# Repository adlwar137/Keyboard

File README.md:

# Custom Keyboard

# 🚧 This is a work in progress 🚧

A custom mechanical keyboard deisgned and built from the ground up

## Features

- Custom PCB designed for the keyboard
- Custom case designed in CAD
- Custom firmware

## Design

### PCB

Designed from scratch in KICAD

### Case

Custom case designed in FreeCAD and 3D printed

## Firmware

Custom firmware the will be written in rust

## Folders

- `firmware/` - Keyboard firmware
- `pcb/` - PCB design files
- `artifacts/` - STLs, DXFs, and other exported files
- `screenshots/` - Screenshots of various parts during development

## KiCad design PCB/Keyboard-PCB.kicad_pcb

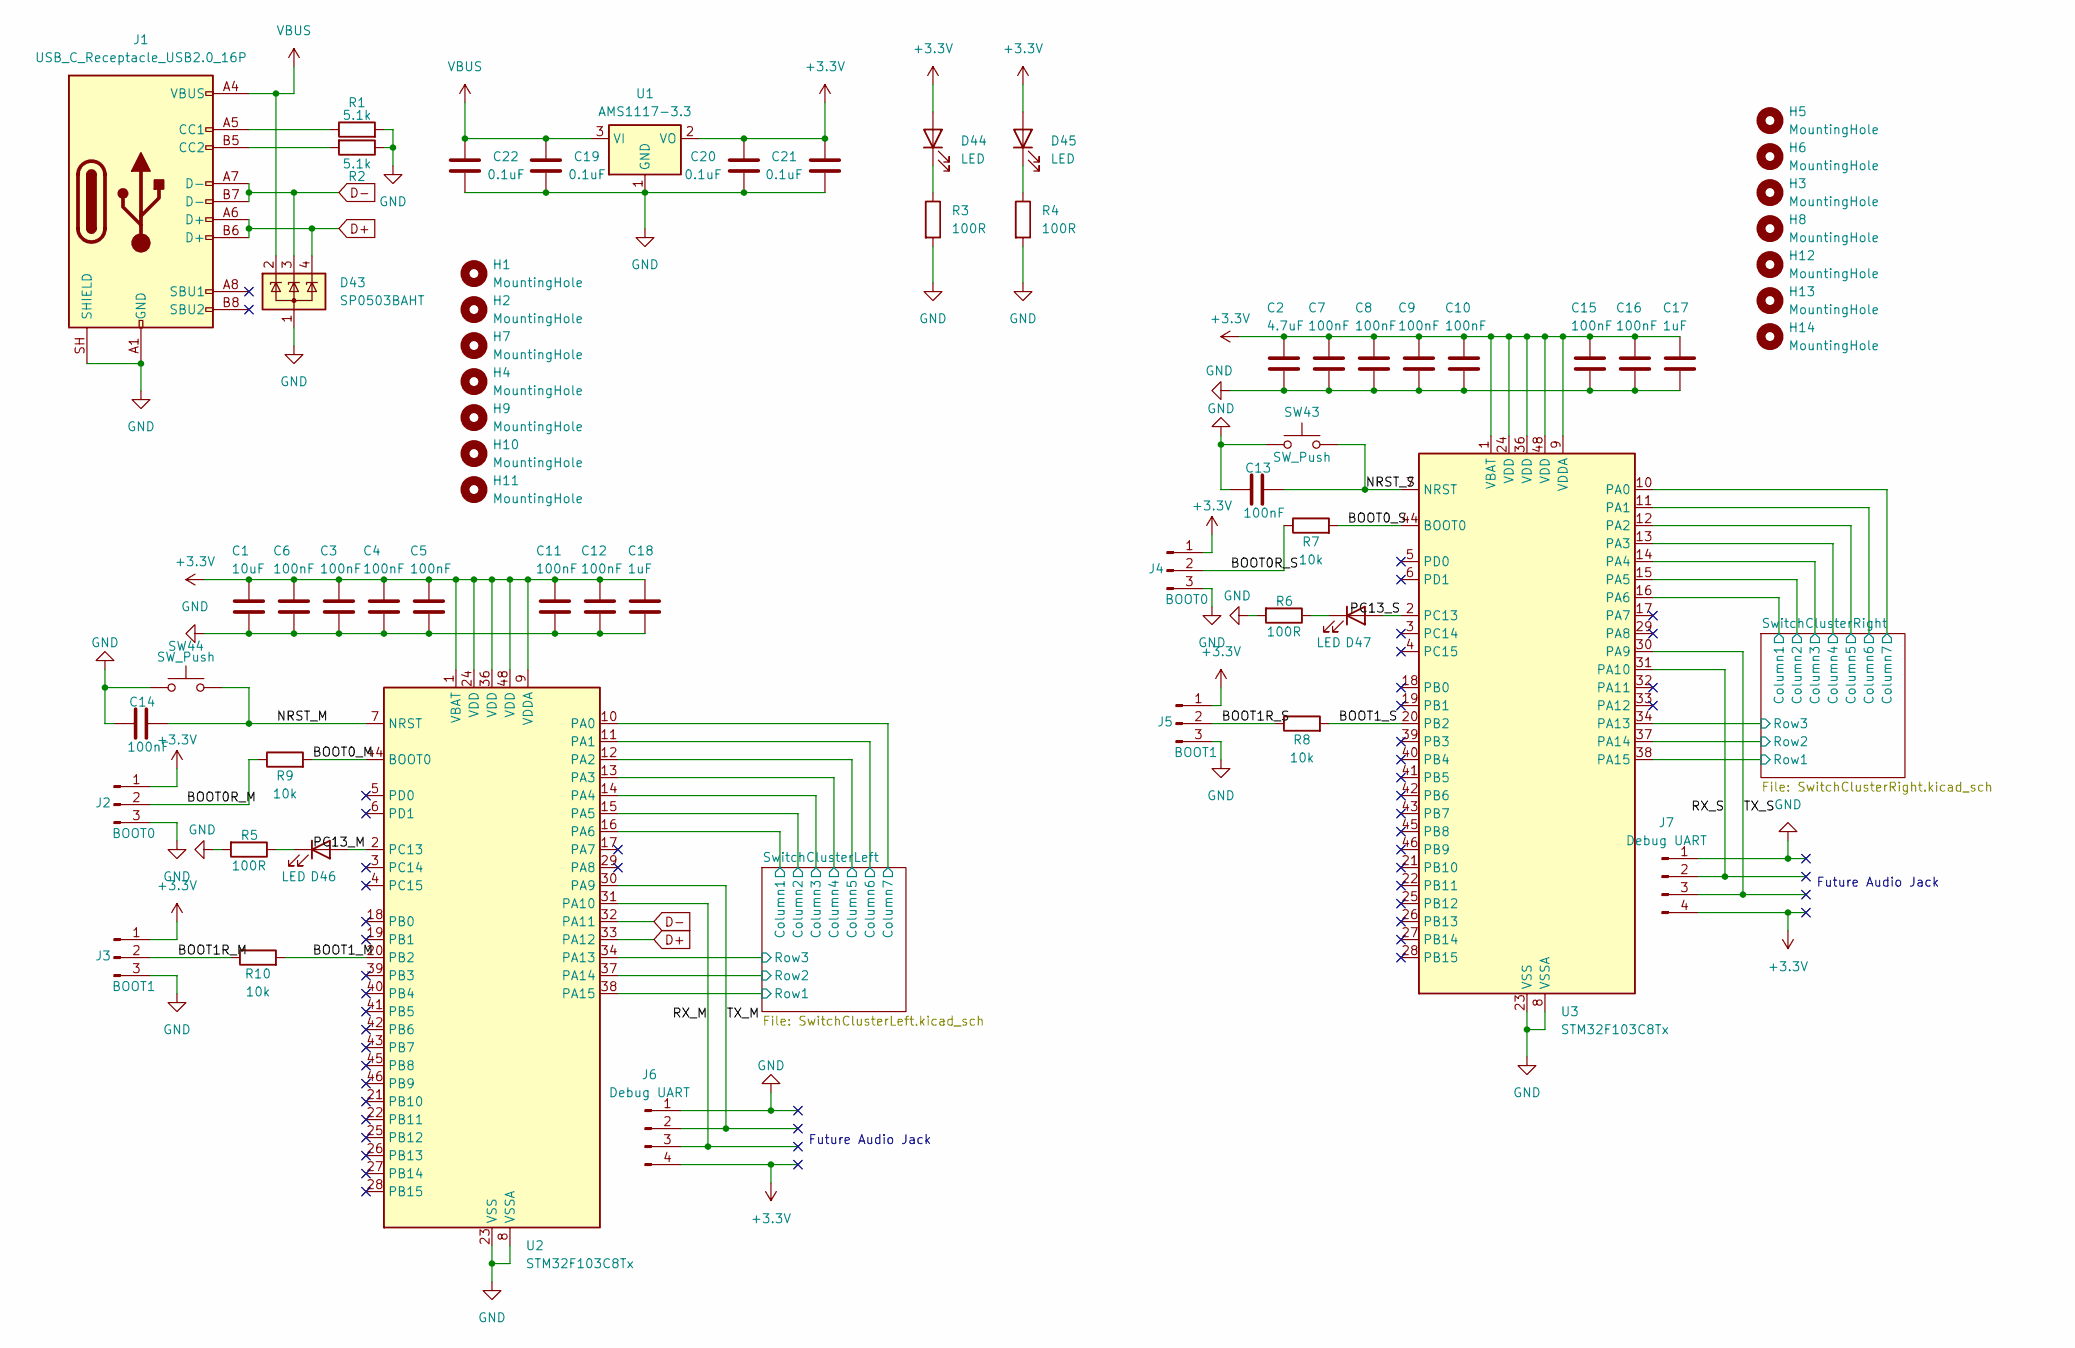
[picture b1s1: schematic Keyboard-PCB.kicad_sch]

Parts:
C1: 10uF; C_0402_1005Metric
C2: 4.7uF; C_0402_1005Metric
C3, C4, C5, C6, C7, C8, C9, C10, C11, C12, C13, C14, C15, C16: 100nF; C_0402_1005Metric
C17, C18: 1uF; C_0402_1005Metric
C19, C20, C21, C22: 0.1uF; C_0402_1005Metric
D43: SP0503BAHT; SOT-143
D44, D45, D46, D47: LED; LED_0805_2012Metric
H1, H2, H3, H4, H5, H6, H7, H8, H9, H10, H11, H12, H13, H14: MountingHole; MountingHole_3mm
J1: USB_C_Receptacle_USB2.0_16P; USB_C_Receptacle_GCT_USB4085
J2, J4: BOOT0; PinHeader_1x03_P2.54mm_Vertical
J3, J5: BOOT1; PinHeader_1x03_P2.54mm_Vertical
J6, J7: Debug UART; PinHeader_1x04_P2.54mm_Vertical
R1, R2: 5.1k; R_0805_2012Metric
R3, R4, R5, R6: 100R; R_0402_1005Metric
R7, R8, R9, R10: 10k; R_0805_2012Metric
SW43, SW44: SW_Push; SW_Push_1P1T_NO_CK_KMR2
U1: AMS1117-3.3; SOT-223-3_TabPin2
U2, U3: STM32F103C8Tx; LQFP-48_7x7mm_P0.5mm

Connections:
+3.3V: C1.1, C2.1, C3.1, C4.1, C5.1, C6.1, C7.1, C8.1, C9.1, C10.1, C11.1, C12.1, C15.1, C16.1, C17.1, C18.1, C20.1, C21.1, D44.2 (A), D45.2 (A), J2.1, J3.1, J4.1, J5.1, J6.4, J7.4, U1.2 (VO), U2.1 (VBAT), U2.9 (VDDA), U2.24 (VDD), U2.36 (VDD), U2.48 (VDD), U3.1 (VBAT), U3.9 (VDDA), U3.24 (VDD), U3.36 (VDD), U3.48 (VDD)
/BOOT0R_M: J2.2, R9.1
/BOOT0R_S: J4.2, R7.1
/BOOT0_M: R9.2, U2.44 (BOOT0)
/BOOT0_S: R7.2, U3.44 (BOOT0)
/BOOT1R_M: J3.2, R10.1
/BOOT1R_S: J5.2, R8.1
/BOOT1_M: R10.2, U2.20 (PB2)
/BOOT1_S: R8.2, U3.20 (PB2)
/NRST_M: C14.1, SW44.2, U2.7 (NRST)
/NRST_S: C13.1, SW43.2, U3.7 (NRST)
/PC13_M: D46.2 (A), U2.2 (PC13)
/PC13_S: D47.2 (A), U3.2 (PC13)
/RX_M: J6.3, U2.31 (PA10)
/RX_S: J7.2, U3.31 (PA10)
/SwitchClusterLeft/Column1: U2.16 (PA6); also elsewhere on the board
/SwitchClusterLeft/Column2: U2.15 (PA5); also elsewhere on the board
/SwitchClusterLeft/Column3: U2.14 (PA4); also elsewhere on the board
/SwitchClusterLeft/Column4: U2.13 (PA3); also elsewhere on the board
/SwitchClusterLeft/Column5: U2.12 (PA2); also elsewhere on the board
/SwitchClusterLeft/Column6: U2.11 (PA1); also elsewhere on the board
/SwitchClusterLeft/Column7: U2.10 (PA0); also elsewhere on the board
/SwitchClusterLeft/Row1: U2.38 (PA15); also elsewhere on the board
/SwitchClusterLeft/Row2: U2.37 (PA14); also elsewhere on the board
/SwitchClusterLeft/Row3: U2.34 (PA13); also elsewhere on the board
/SwitchClusterRight/Column1: U3.16 (PA6); also elsewhere on the board
/SwitchClusterRight/Column2: U3.15 (PA5); also elsewhere on the board
/SwitchClusterRight/Column3: U3.14 (PA4); also elsewhere on the board
/SwitchClusterRight/Column4: U3.13 (PA3); also elsewhere on the board
/SwitchClusterRight/Column5: U3.12 (PA2); also elsewhere on the board
/SwitchClusterRight/Column6: U3.11 (PA1); also elsewhere on the board
/SwitchClusterRight/Column7: U3.10 (PA0); also elsewhere on the board
/SwitchClusterRight/Row1: U3.38 (PA15); also elsewhere on the board
/SwitchClusterRight/Row2: U3.37 (PA14); also elsewhere on the board
/SwitchClusterRight/Row3: U3.34 (PA13); also elsewhere on the board
/TX_M: J6.2, U2.30 (PA9)
/TX_S: J7.3, U3.30 (PA9)
D+: D43.4 (K), J1.A6 (D+), J1.B6 (D+), U2.33 (PA12)
D-: D43.3 (K), J1.A7 (D-), J1.B7 (D-), U2.32 (PA11)
GND: C1.2, C2.2, C3.2, C4.2, C5.2, C6.2, C7.2, C8.2, C9.2, C10.2, C11.2, C12.2, C13.2, C14.2, C15.2, C16.2, C17.2, C18.2, C19.2, C20.2, C21.2, C22.2, D43.1 (A), J1.A1 (GND), J1.A12 (GND), J1.B1 (GND), J1.B12 (GND), J1.SH (SHIELD), J2.3, J3.3, J4.3, J5.3, J6.1, J7.1, R1.2, R2.1, R3.2, R4.2, R5.2, R6.2, SW43.1, SW44.1, U1.1 (GND), U2.8 (VSSA), U2.23 (VSS), U2.35 (VSS), U2.47 (VSS), U3.8 (VSSA), U3.23 (VSS), U3.35 (VSS), U3.47 (VSS)
unnamed: D44.1 (K), R3.1
unnamed: D45.1 (K), R4.1
unnamed: D46.1 (K), R5.1
unnamed: D47.1 (K), R6.1
unnamed: J1.A5 (CC1), R1.1
unnamed: J1.B5 (CC2), R2.2
VBUS: C19.1, C22.1, D43.2 (K), J1.A4 (VBUS), J1.A9 (VBUS), J1.B4 (VBUS), J1.B9 (VBUS), U1.3 (VI)

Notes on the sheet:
Future Audio Jack

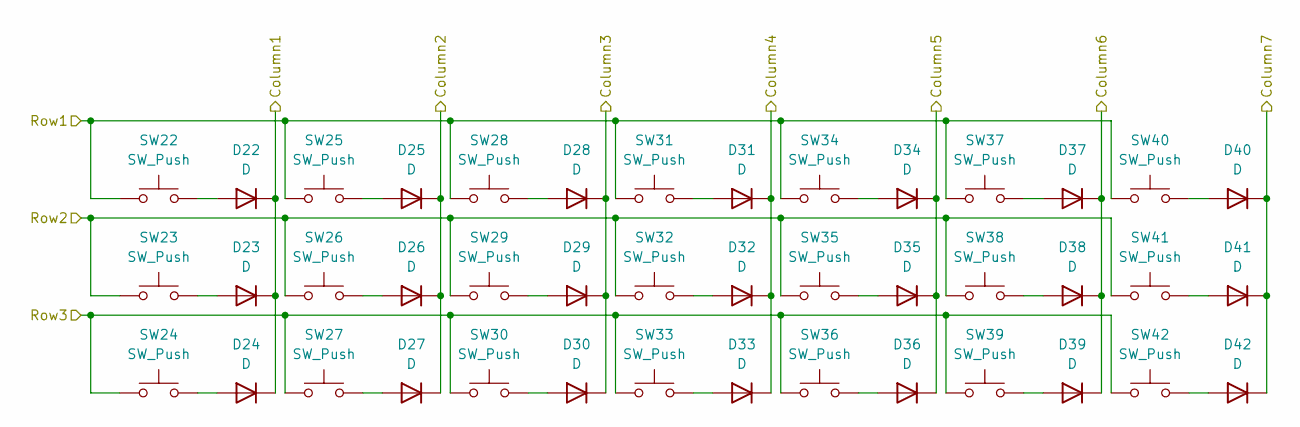
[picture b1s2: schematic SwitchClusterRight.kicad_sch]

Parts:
D22, D23, D24, D25, D26, D27, D28, D29, D30, D31, D32, D33, D34, D35, D36, D37, D38, D39, D40, D41, D42: D; D_0805_2012Metric
SW22, SW23, SW24, SW25, SW26, SW27, SW28, SW29, SW30, SW31, SW32, SW33, SW34, SW35, SW36, SW37, SW38, SW39, SW40, SW41, SW42: SW_Push; MX100H

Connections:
/SwitchClusterRight/Column1: D22.1 (K), D23.1 (K), D24.1 (K); also elsewhere on the board
/SwitchClusterRight/Column2: D25.1 (K), D26.1 (K), D27.1 (K); also elsewhere on the board
/SwitchClusterRight/Column3: D28.1 (K), D29.1 (K), D30.1 (K); also elsewhere on the board
/SwitchClusterRight/Column4: D31.1 (K), D32.1 (K), D33.1 (K); also elsewhere on the board
/SwitchClusterRight/Column5: D34.1 (K), D35.1 (K), D36.1 (K); also elsewhere on the board
/SwitchClusterRight/Column6: D37.1 (K), D38.1 (K), D39.1 (K); also elsewhere on the board
/SwitchClusterRight/Column7: D40.1 (K), D41.1 (K), D42.1 (K); also elsewhere on the board
/SwitchClusterRight/Row1: SW22.2, SW25.2, SW28.2, SW31.2, SW34.2, SW37.2, SW40.2; also elsewhere on the board
/SwitchClusterRight/Row2: SW23.2, SW26.2, SW29.2, SW32.2, SW35.2, SW38.2, SW41.2; also elsewhere on the board
/SwitchClusterRight/Row3: SW24.2, SW27.2, SW30.2, SW33.2, SW36.2, SW39.2, SW42.2; also elsewhere on the board
unnamed: D22.2 (A), SW22.1
unnamed: D23.2 (A), SW23.1
unnamed: D24.2 (A), SW24.1
unnamed: D25.2 (A), SW25.1
unnamed: D26.2 (A), SW26.1
unnamed: D27.2 (A), SW27.1
unnamed: D28.2 (A), SW28.1
unnamed: D29.2 (A), SW29.1
unnamed: D30.2 (A), SW30.1
unnamed: D31.2 (A), SW31.1
unnamed: D32.2 (A), SW32.1
unnamed: D33.2 (A), SW33.1
unnamed: D34.2 (A), SW34.1
unnamed: D35.2 (A), SW35.1
unnamed: D36.2 (A), SW36.1
unnamed: D37.2 (A), SW37.1
unnamed: D38.2 (A), SW38.1
unnamed: D39.2 (A), SW39.1
unnamed: D40.2 (A), SW40.1
unnamed: D41.2 (A), SW41.1
unnamed: D42.2 (A), SW42.1

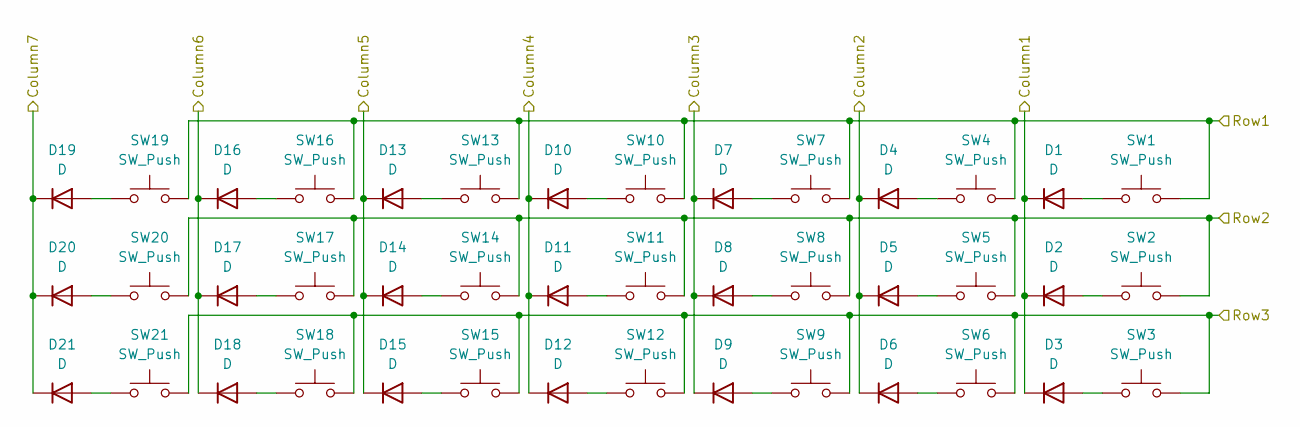
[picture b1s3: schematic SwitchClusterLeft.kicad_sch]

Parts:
D1, D2, D3, D4, D5, D6, D7, D8, D9, D10, D11, D12, D13, D14, D15, D16, D17, D18, D19, D20, D21: D; D_0805_2012Metric
SW1, SW2, SW3, SW4, SW5, SW6, SW7, SW8, SW9, SW10, SW11, SW12, SW13, SW14, SW15, SW16, SW17, SW18, SW19, SW20, SW21: SW_Push; MX100H

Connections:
/SwitchClusterLeft/Column1: D1.1 (K), D2.1 (K), D3.1 (K); also elsewhere on the board
/SwitchClusterLeft/Column2: D4.1 (K), D5.1 (K), D6.1 (K); also elsewhere on the board
/SwitchClusterLeft/Column3: D7.1 (K), D8.1 (K), D9.1 (K); also elsewhere on the board
/SwitchClusterLeft/Column4: D10.1 (K), D11.1 (K), D12.1 (K); also elsewhere on the board
/SwitchClusterLeft/Column5: D13.1 (K), D14.1 (K), D15.1 (K); also elsewhere on the board
/SwitchClusterLeft/Column6: D16.1 (K), D17.1 (K), D18.1 (K); also elsewhere on the board
/SwitchClusterLeft/Column7: D19.1 (K), D20.1 (K), D21.1 (K); also elsewhere on the board
/SwitchClusterLeft/Row1: SW1.2, SW4.2, SW7.2, SW10.2, SW13.2, SW16.2, SW19.2; also elsewhere on the board
/SwitchClusterLeft/Row2: SW2.2, SW5.2, SW8.2, SW11.2, SW14.2, SW17.2, SW20.2; also elsewhere on the board
/SwitchClusterLeft/Row3: SW3.2, SW6.2, SW9.2, SW12.2, SW15.2, SW18.2, SW21.2; also elsewhere on the board
unnamed: D1.2 (A), SW1.1
unnamed: D2.2 (A), SW2.1
unnamed: D3.2 (A), SW3.1
unnamed: D4.2 (A), SW4.1
unnamed: D5.2 (A), SW5.1
unnamed: D6.2 (A), SW6.1
unnamed: D7.2 (A), SW7.1
unnamed: D8.2 (A), SW8.1
unnamed: D9.2 (A), SW9.1
unnamed: D10.2 (A), SW10.1
unnamed: D11.2 (A), SW11.1
unnamed: D12.2 (A), SW12.1
unnamed: D13.2 (A), SW13.1
unnamed: D14.2 (A), SW14.1
unnamed: D15.2 (A), SW15.1
unnamed: D16.2 (A), SW16.1
unnamed: D17.2 (A), SW17.1
unnamed: D18.2 (A), SW18.1
unnamed: D19.2 (A), SW19.1
unnamed: D20.2 (A), SW20.1
unnamed: D21.2 (A), SW21.1

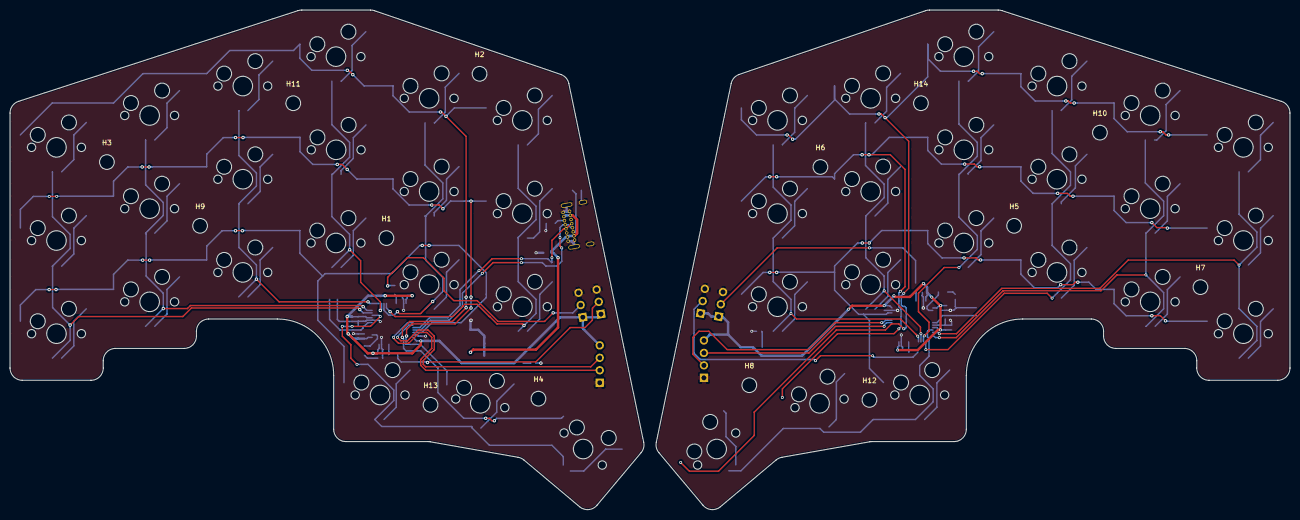
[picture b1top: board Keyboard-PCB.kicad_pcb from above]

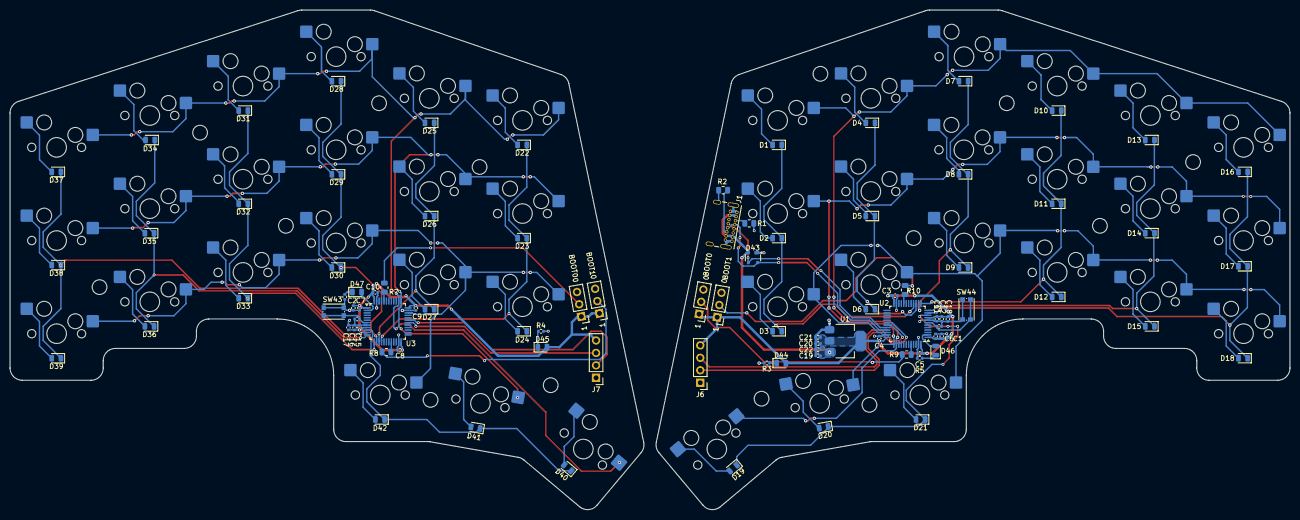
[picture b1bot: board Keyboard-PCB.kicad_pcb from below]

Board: 2 copper layers, 261.0 x 101.9 mm, 147 parts (133 on the bottom side), 89 nets.
